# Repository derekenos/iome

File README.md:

# I/O <-> ME

iome is a platform for developing physical interfaces with a web application frontend using modern, off-the-shelf technologies.

The overall system looks like:

```
 ______________________          _____________________                      _________________________
| Buttons, Knobs, etc. |  --->  | Wifi-enabled micro- |  <-- WiFi ------>  | Device with a display   |
 ----------------------         | controller running  |           | \      | and a web browser, e.g. |
 ____________________           | an HTTP server and  |           |  OR    | phone, tablet, computer |
| LEDs, Motors, etc. |  <-----  | minimal web applic- |           |         --------------------------
 --------------------           | ation framework     |           |               /\   
                                 ---------------------        [ Router ] ---------'
```

## Applications

This was created specificially to serve as a wireless HTML5 game console:

More generally, it enables wireless access to physical switch, knob, etc. data via a [Websocket](https://developer.mozilla.org/en-US/docs/Web/API/WebSockets_API).

This means that you can:

1. Build/buy something like the [Dev Kit v1](https://github.com/derekenos/iome/tree/master/dev_kits/v1)
2. [Load it up with the `iome` software](https://github.com/derekenos/iome/tree/master/dev_kits/v1#loading-the-firmware-onto-the-esp32) (if necessary)
3. Power it up
4. Connect your computer to the `iome-{theUniqueId}` Wifi Access Point that it creates by default
5. Surf your browser over to `http://192.168.4.1`
6. Open the browser dev console and do:
```
const ws = new WebSocket(`ws://192.168.4.1/input`)
ws.onmessage = e => {
  const data = JSON.parse(e.data)
  console.log(data)
}
```
7. Watch the data change as you interact with the physical buttons, knob, etc.

From there, you can integrate that WebSocket hook into whatever web application code you want.

### Connect to an Existing Wifi Access Point

The default configuration [creates an Access Point on boot](https://github.com/derekenos/iome/blob/master/dev_kits/v1/filesystem/config.json#L7-L8), but you can edit the config to [specify that it connect to an existing Access Point instead](https://github.com/derekenos/iome/blob/master/dev_kits/v1/filesystem/config.json#L9-L11). You can use the editor [described here](https://github.com/derekenos/femtoweb/#in-browser-file-editor) to do this. Once connected, you should, providing your AP supports [mDNS](http://multicastdns.org/), be able to access it via `http://iome-{uniqueId}.local`, as opposed to having to discover and specify its IP address.

## [Dev Kit v1](https://github.com/derekenos/iome/tree/master/dev_kits/v1)

This first development kit features a familiar household rotary push-button dimmer knob as its primary physical input and three [living hinge](https://en.wikipedia.org/wiki/Living_hinge) tactile switch buttons (labelled 1, 2, 3). It employs the popular, low-cost ESP32 running Micropython as the brains of the operation.

## [Sketchy](https://github.com/derekenos/iome/tree/master/appliances/sketchy)

Sketchy is a motorized Etch A Sketch display appliance.

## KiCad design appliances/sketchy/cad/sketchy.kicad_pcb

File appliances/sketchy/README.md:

# Sketchy

Sketchy is a motorized Etch A Sketch display appliance.

## Bill of Materials

| Quantity | Description | Manufacturer | Part Number | Approx. Total Cost (USD) |
| --- | --- | --- | --- | --- |
| 1 | Etch A Sketch | | [20083951-6041762](https://www.amazon.com/gp/product/B01MTS465O) | $10 |
| 1 | Wifi Dev Board | Espressif | [ESP32-PICO-KIT](https://octopart.com/esp32-pico-kit-espressif+systems-91893718) | $10 |
| 2 | StepStick Motor Driver | GENERIC | [B01FFGAKK8](https://www.amazon.com/gp/product/B01FFGAKK8) | $5 |
| 2 | Nema 17 Stepper Motors | STEPPERONLINE | [17HS16-2004S](https://www.amazon.com/gp/product/B00PNEQI7W) | $26 |
| 2 | 6mm Bore GT2 Pulley | Houkr | [B07DMZQ364](https://www.amazon.com/gp/product/B07DMZQ364) | $4 |
| 2 | 5mm Bore GT2 Pulley | WINSINN | [B077GNZK3J](https://www.amazon.com/WINSINN-Aluminum-Synchronous-Timing-Printer/dp/B077GNZK3J) | $3 |
| 2 | Closed Loop GT2 Belt | Linglong | [B07L16H5WN](https://www.amazon.com/gp/product/B07L16H5WN) | $2 |
| 1 | DC Power Jack | CUI |  [PJ-102AH](https://octopart.com/search?q=+PJ-102AH&currency=USD&specs=0) | $0.75 |
| 1 | PCB | Circuit Board | [JLCPCB](https://jlcpcb.com/) | $2 |
| 1 | 9V Power Supply | TB Tbuymax  | [B06Y1LF8T5](https://www.amazon.com/gp/product/B06Y1LF8T5) | $9 |
| 8 | M3 x 8mm Socket Head Screw | McMASTER-CARR | [91292a112](https://www.mcmaster.com/91292a112) | $0.36 |
| 1 | Laser-cut front panel | ? | ? | ? |
| 4 | Short Wood Screws | ? | ? | ? |

Approx. Total Cost: $72

## View of Materials

## Professional Electrical Interconnection Diagram

## The Printed Board of Circuits

## The Enclosure

## Loading the Firmware onto the ESP32

See the [Dev Kit v1 instructions](https://github.com/derekenos/iome/tree/master/dev_kits/v1#loading-the-firmware-onto-the-esp32).

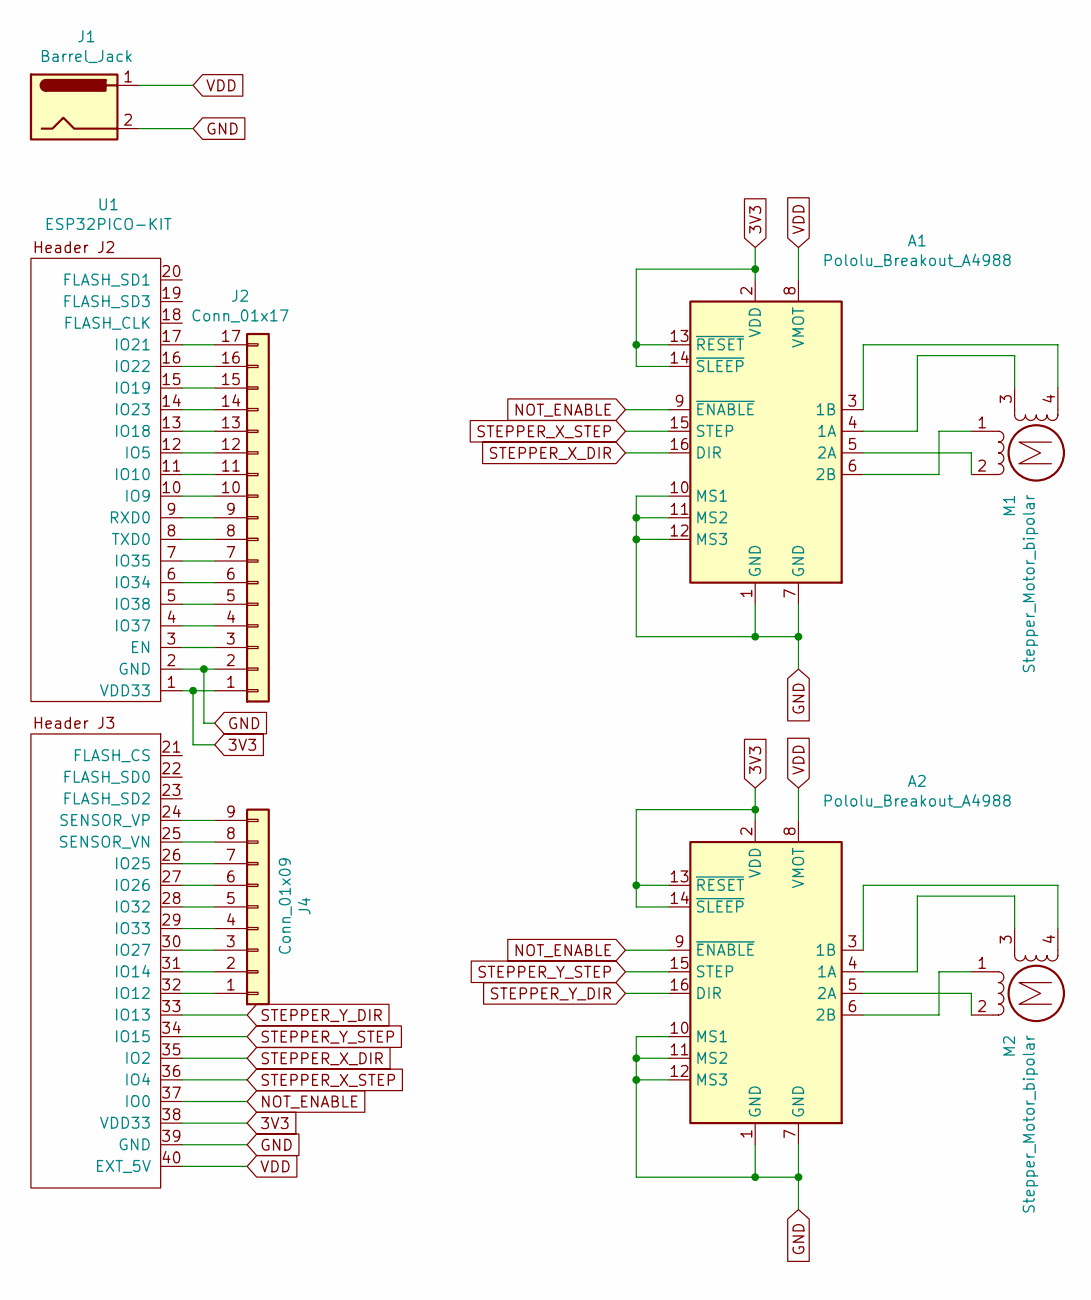
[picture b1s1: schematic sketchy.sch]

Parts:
A1, A2: Pololu_Breakout_A4988; Pololu_Breakout-16_15.2x20.3mm
J1: Barrel_Jack; Barrel_Jack_CUI_PJ-102AH
J2: Conn_01x17
J4: Conn_01x09; Pin_Header_Straight_1x09_Pitch2.54mm
M1, M2: Stepper_Motor_bipolar; Pin_Header_Angled_1x04_Pitch2.54mm
U1: ESP32PICO-KIT; ESP32-PICO-KIT

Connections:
3V3: A1.2 (VDD), A1.13 (~RESET), A1.14 (~SLEEP), A2.2 (VDD), A2.13 (~RESET), A2.14 (~SLEEP), J2.1, U1.1 (VDD33), U1.38 (VDD33)
GND: A1.1 (GND), A1.7 (GND), A1.10 (MS1), A1.11 (MS2), A1.12 (MS3), A2.1 (GND), A2.7 (GND), A2.10 (MS1), A2.11 (MS2), A2.12 (MS3), J1.2, J2.2, U1.2 (GND), U1.39 (GND)
NOT_ENABLE: A1.9 (~ENABLE), A2.9 (~ENABLE), U1.37 (IO0)
unnamed: A1.3 (1B), M1.4
unnamed: A1.4 (1A), M1.3
unnamed: A1.5 (2A), M1.2 (-)
unnamed: A1.6 (2B), M1.1
unnamed: A2.3 (1B), M2.4
unnamed: A2.4 (1A), M2.3
unnamed: A2.5 (2A), M2.2 (-)
unnamed: A2.6 (2B), M2.1
unnamed: J2.3, U1.3 (EN)
unnamed: J2.4, U1.4 (IO37)
unnamed: J2.5, U1.5 (IO38)
unnamed: J2.6, U1.6 (IO34)
unnamed: J2.7, U1.7 (IO35)
unnamed: J2.8, U1.8 (TXD0)
unnamed: J2.9, U1.9 (RXD0)
unnamed: J2.10, U1.10 (IO9)
unnamed: J2.11, U1.11 (IO10)
unnamed: J2.12, U1.12 (IO5)
unnamed: J2.13, U1.13 (IO18)
unnamed: J2.14, U1.14 (IO23)
unnamed: J2.15, U1.15 (IO19)
unnamed: J2.16, U1.16 (IO22)
unnamed: J2.17, U1.17 (IO21)
unnamed: J4.1, U1.32 (IO12)
unnamed: J4.2, U1.31 (IO14)
unnamed: J4.3, U1.30 (IO27)
unnamed: J4.4, U1.29 (IO33)
unnamed: J4.5, U1.28 (IO32)
unnamed: J4.6, U1.27 (IO26)
unnamed: J4.7, U1.26 (IO25)
unnamed: J4.8, U1.25 (SENSOR_VN)
unnamed: J4.9, U1.24 (SENSOR_VP)
STEPPER_X_DIR: A1.16 (DIR), U1.35 (IO2)
STEPPER_X_STEP: A1.15 (STEP), U1.36 (IO4)
STEPPER_Y_DIR: A2.16 (DIR), U1.33 (IO13)
STEPPER_Y_STEP: A2.15 (STEP), U1.34 (IO15)
VDD: A1.8 (VMOT), A2.8 (VMOT), J1.1, U1.40 (EXT_5V)

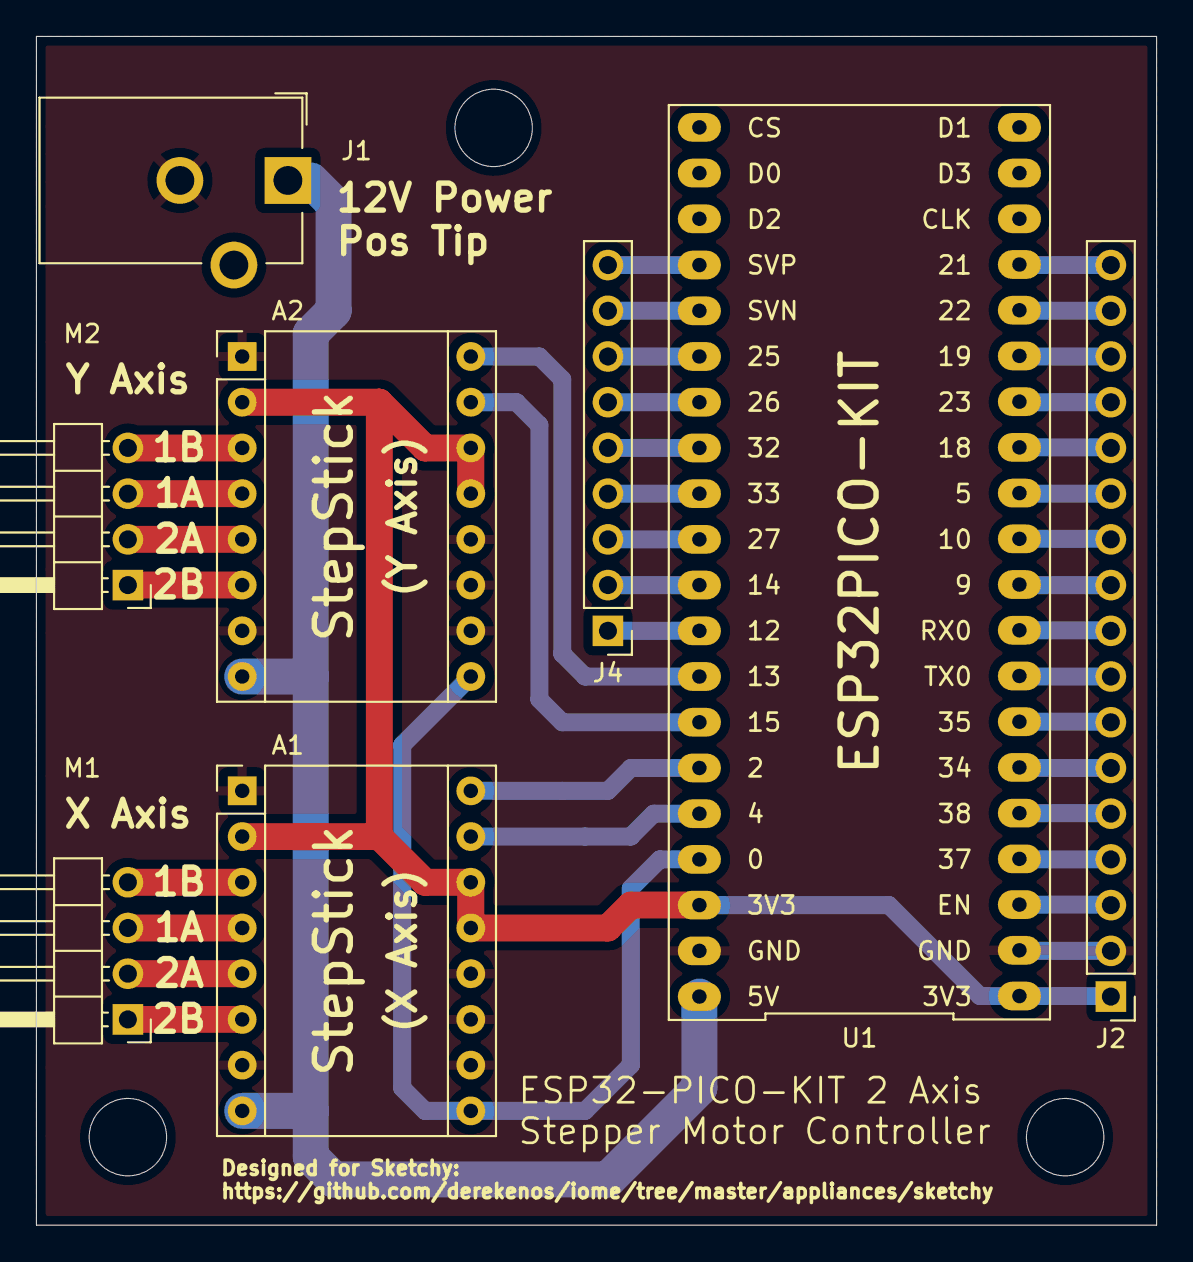
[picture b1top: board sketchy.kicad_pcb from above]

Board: 2 copper layers, 62.2 x 66.0 mm, 8 parts (0 on the bottom side), 40 nets.

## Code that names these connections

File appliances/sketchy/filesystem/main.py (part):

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STEPPER_NOT_ENABLE_PIN = Pin(0, Pin.OUT)
STEPPER_NOT_ENABLE_PIN.value(1)

STEPPER_X_STEP_PIN = Pin(4, Pin.OUT)
STEPPER_X_STEP_PIN.value(0)

STEPPER_X_DIR_PIN = Pin(2, Pin.OUT)
STEPPER_X_DIR_PIN.value(1)

STEPPER_Y_STEP_PIN = Pin(15, Pin.OUT)
STEPPER_Y_STEP_PIN.value(0)

STEPPER_Y_DIR_PIN = Pin(13, Pin.OUT)
STEPPER_Y_DIR_PIN.value(1)

DATA_PATH = '/data'
LAST_POSITION_DATA_PATH = path.join(DATA_PATH, 'last_position')
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            if x_pos == X_AXIS_MAX:
                return False
            x_pos += 1
        step_pin = STEPPER_X_STEP_PIN
        dir_pin = STEPPER_X_DIR_PIN
    else:
        if direction == DIR_DOWN:
            if y_pos == 0:
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            if y_pos == Y_AXIS_MAX:
                return False
            y_pos += 1
        step_pin = STEPPER_Y_STEP_PIN
        dir_pin = STEPPER_Y_DIR_PIN

    dir_pin(0 if direction in (DIR_DOWN, DIR_LEFT) else 1)

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
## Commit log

2019-10-24 Submodules now use HTTPS URLs
2019-11-09 WIP etch-a-sketch display appliance
2019-11-14 Added WIP enclosure
2019-11-14 Added some motion control HTTP endpoints.
2019-11-14 Change SSID and host name to plain ol' 'sketchy'
2019-11-15 Legitimized Sketchy submodules.
2019-11-15 Roped in version of femtoweb that adds query param parsing and modified main._multi_step() to use it. Roped in new, barebones public sketchy branch.
2019-11-15 Roped in new version of micropython-docker that refactors the configure-device script
2019-11-15 Fixed stepper direction bug. Made _move_to_point() use query parsers.
2019-11-17 Move step_toward_point() logic into move_to_point() and added simple linear interpolation.
2019-11-17 Removed iome-public submodule and created standalone public/ dir with index.html that implements a single canvas-based move-to-point app.
2019-11-18 Added /draw endpoint that accepts a websocket connection and and mousemove listener to the index.html canvas that kinda results in realtime remote drawing.
2019-11-18 Add version of femtoweb that adds websocket support.
2019-11-20 Added /home endpoint and terrible SVG render function that basically works.
2019-11-20 Added the file to render as a query param to demo_svg endpoint.
2019-11-20 Added path closing support to render_svg()
2019-11-21 Made the /demo text a little bigger and added Go Home button to index.html
2019-11-21 Removed accidentally added Dockerfile
2019-11-21 Fixed access point name in Makefile
2019-11-24 Added enclosure PNG to README.
2019-11-24 Fixed misspelling in enclosure PNG print layer text.
2019-11-24 Fixed misspelling in the dev kit enclosure SVG print layer text and added the same text to the sketchy SVG.
2019-11-27 WIP Sketchy Kicad PCB
2019-11-27 Changed stepper driver to the 4988 that I'm actually using, routed all tracks, and added silkscreen text and mounting holes.
2019-11-27 Updated code pin mapping to reflect PCB-routing-related changes.
2019-11-28 Created denser (v2) PCB
2019-11-29 Created smaller, square PCB with easy access to ESP32-PICO-KIT USB port.
2019-11-30 Added schematic image
2019-11-30 Fixed the schematic image.
2019-11-30 Removed rogue schematic connection between GND and 3V3 at ESP32-PICO-KIT pin 1 / header junction. Luckily, it doesn't appear as though that connection was ever propagated to the PCB.
2019-12-05 Updated BOM to reflect new custom PCB.
2019-12-05 Fixed broken Sketchy BOM stepper motor link
2019-12-08 Removed the StepStick link from the BOM because the linked product had an incompatible footprint.
2019-12-12 Moved take_while() and drop_while() into a new utils.py, added tests, and fixed bug.
2019-12-12 Created utils.first_false_index() and added a test.
2019-12-12 WIP - generalize SVG parser
2019-12-12 Now parsing one float at a time from the path d string instead of coordinate pairs.
2019-12-12 Added View of Materials
2019-12-12 Added Amazon link for the StepSticks
2019-12-12 WIP custom fontset
2019-12-13 Finished first pass on default uppercase letters. Added supported for multiple revisit_map values. Modified /demo to use the new font.
2019-12-14 Added /write HTTP endpoint, backlash compensation, and a space character.
2019-12-15 Added uniform character scaling and SPACE/unsupported character handling.
2019-12-15 Better backlash compensation and new demo text
2019-12-31 Fixed .../sketchy/micropython-docker submodule config
2020-01-25 Added annotated kit SVG
2020-01-25 WIP - save actuator position for recall on power up
2020-01-25 Added Sketchy PCB mount
2020-08-08 WIP Weezel
2020-08-08 Added calc_legs() function.
2020-08-08 First working kinematics. Added weezel micropython-docker submodule.
2020-08-08 Fixed the HTML drawing canvas to work with weezel
2020-08-08 Reduced Y_MAX because the lower region renders the belts slack and slippy. Fixed move inverted-y font stuff. Added a trace_perimeter HTTP endpoint.
2020-08-09 Fixed a couple of bugs and increased inter-step delay.
2020-08-09 WIP v3 sled
2020-08-09 4 ms seems like a good interstep delay.
2020-08-09 Pretty good v3 sled z axis slider cut.
2020-08-10 Improved sled v3 frame.
2020-08-10 Added belt catch riser to compensate for the sled v3 z-axis wrt center of balance.
2020-08-10 WIP gcode parser
2020-08-10 Apparently working basic gcode parser.
2020-08-10 Added untested execute_gcode endpoint and started reimplmenting things that micropython doesn't support, like enum, and named and noncapturing re groups, etc.
2020-08-10 First working gcode rendering
2020-08-10 Now inverting gcode Y axis to make things look right that jscut generates.
2020-08-11 Added device holder bracket
2020-08-11 Added untested 3D sled cap.
2020-08-12 Modified z-axis stepper panel to accomodate the new motor, added a elastic band catch, and modied the finger sockets to not be so tight.
2020-08-12 Modified z-axis plunger to add an elastic band catch, modied the finger sockets to not be so tight, and modified some other dimensions too just for fun.
2020-08-12 Modified sled frame z-axis slot of be a little less tight.
2020-08-13 First working z-axis servo control.
2020-08-13 Adjusted the max X / Y values
2020-08-14 Add ability to save last known position and route decorator that uses it. Added reset_home endpoint to set the current location as 0, 0
2020-08-14 Changed interstep delay from 4 to 8 which results in much cleaner draws. Changed default z position to up.
2020-08-15 Consolidated global state variables into State class and removed last_known_position DATAFILE in favor of STATE. Consolidated save_final_position and into new motion_operation decorator. Removed SVG 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
2020-08-15 Moved motion_operator decorators to larger-operation draw_text and execute_gcode functions.
2020-08-15 Added weezel femtoweb submodule
2020-08-15 Big refactor. Converted things into classes and made the canvas drawing interfacing lift pen when appropriate.
2020-08-15 Added more buttons to the web interface
2021-10-12 Fixed broken Sketchy README video link
